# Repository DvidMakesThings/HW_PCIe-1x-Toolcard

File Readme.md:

# PCIe-1x-Toolcard Project

## Contents
This folder contains all the documents related to the PCIe-1x-Toolcard project.

## Usage
To use the files in this project, navigate to the respective directories and follow the instructions provided in each document.

## License
This project is licensed under the GPL-3.0 License. See the [LICENSE](LICENSE) file for details.

## Contact
For questions or feedback:
- Email: [s.dvid@hotmail.com](mailto:s.dvid@hotmail.com)
- GitHub: [DvidMakesThings](https://github.com/DvidMakesThings)

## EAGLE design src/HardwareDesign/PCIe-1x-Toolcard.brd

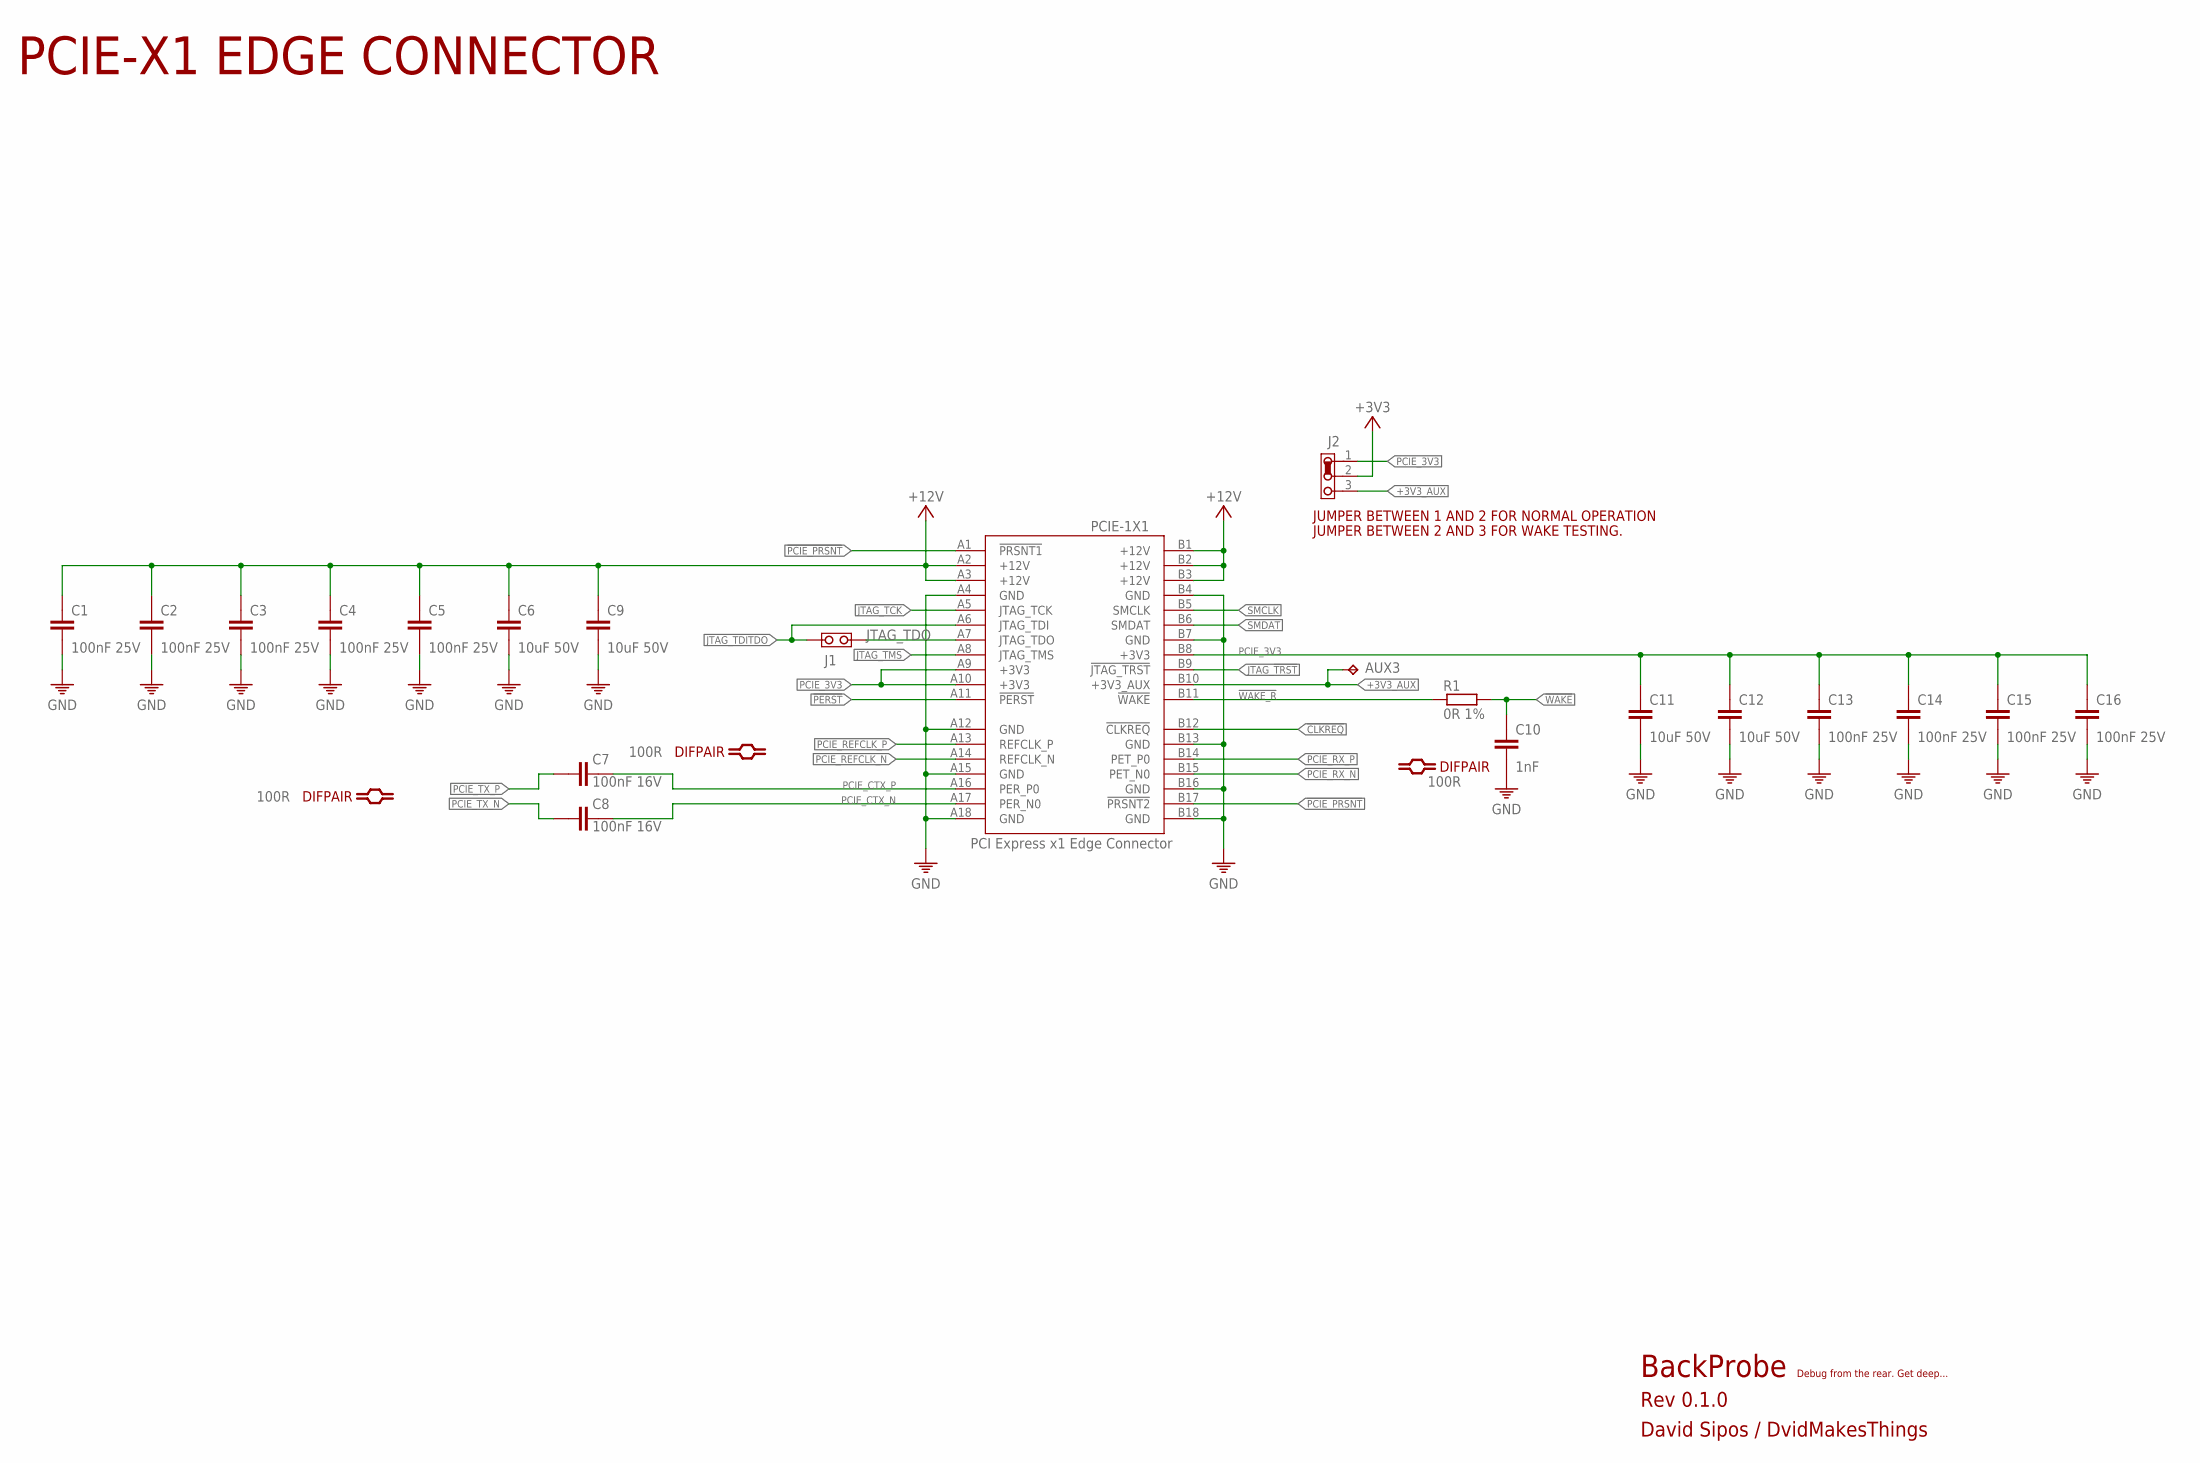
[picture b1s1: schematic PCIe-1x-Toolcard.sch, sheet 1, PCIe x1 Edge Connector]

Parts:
AUX3: TPB1,27; B1,27
C1, C2, C3, C4, C5, C13, C14, C15, C16: 100nF 25V; 0402
C6, C9, C11, C12: 10uF 50V; 0805
C7, C8: 100nF 16V; 0201
C10: 1nF; C0402
J1: JUMPER-NO; J-0402-NO
J2: JUMPER-3
PCIE-1X1: PCI Express x1 Edge Connector; PCIE_X1_LOWPROFILE
R1: 0R 1%; 0201

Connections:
!CLKREQ: PCIE-1X1.B12 (!CLKREQ)
!PCIE_PRSNT: PCIE-1X1.A1 (!PRSNT1), PCIE-1X1.B17 (!PRSNT2)
!PERST: PCIE-1X1.A11 (!PERST); also elsewhere on the board
!WAKE: C10.1, R1.2; also elsewhere on the board
!WAKE_R: PCIE-1X1.B11 (!WAKE), R1.1
+3V3: J2.2; also elsewhere on the board
+3V3_AUX: AUX3.TP, J2.3, PCIE-1X1.B10 (+3V3_AUX)
+12V: C1.1, C2.1, C3.1, C4.1, C5.1, C6.1, C9.1, PCIE-1X1.A2 (+12V), PCIE-1X1.A3 (+12V), PCIE-1X1.B1 (+12V), PCIE-1X1.B2 (+12V), PCIE-1X1.B3 (+12V); also elsewhere on the board
GND: C1.2, C2.2, C3.2, C4.2, C5.2, C6.2, C9.2, C10.2, C11.2, C12.2, C13.2, C14.2, C15.2, C16.2, PCIE-1X1.A4 (GND), PCIE-1X1.A12 (GND), PCIE-1X1.A15 (GND), PCIE-1X1.A18 (GND), PCIE-1X1.B4 (GND), PCIE-1X1.B7 (GND), PCIE-1X1.B13 (GND), PCIE-1X1.B16 (GND), PCIE-1X1.B18 (GND); also elsewhere on the board
JTAG_!TRST: PCIE-1X1.B9 (!JTAG_TRST)
JTAG_TCK: PCIE-1X1.A5 (JTAG_TCK)
JTAG_TDITDO: J1.1, PCIE-1X1.A6 (JTAG_TDI)
JTAG_TDO: J1.2, PCIE-1X1.A7 (JTAG_TDO)
JTAG_TMS: PCIE-1X1.A8 (JTAG_TMS)
PCIE_3V3: C11.1, C12.1, C13.1, C14.1, C15.1, C16.1, J2.1, PCIE-1X1.A9 (+3V3), PCIE-1X1.A10 (+3V3), PCIE-1X1.B8 (+3V3)
PCIE_CTX_N: C8.2, PCIE-1X1.A17 (PER_N0)
PCIE_CTX_P: C7.2, PCIE-1X1.A16 (PER_P0)
PCIE_REFCLK_N: PCIE-1X1.A14 (REFCLK_N); also elsewhere on the board
PCIE_REFCLK_P: PCIE-1X1.A13 (REFCLK_P); also elsewhere on the board
PCIE_RX_N: PCIE-1X1.B15 (PET_N0); also elsewhere on the board
PCIE_RX_P: PCIE-1X1.B14 (PET_P0); also elsewhere on the board
PCIE_TX_N: C8.1; also elsewhere on the board
PCIE_TX_P: C7.1; also elsewhere on the board
SMCLK: PCIE-1X1.B5 (SMCLK)
SMDAT: PCIE-1X1.B6 (SMDAT)

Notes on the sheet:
BackProbe
Rev 0.1.0
David Sipos / DvidMakesThings
Debug from the rear. Get deep...
JUMPER BETWEEN 2 AND 3 FOR WAKE TESTING.
JUMPER BETWEEN 1 AND 2 FOR NORMAL OPERATION
PCIE-X1 EDGE CONNECTOR

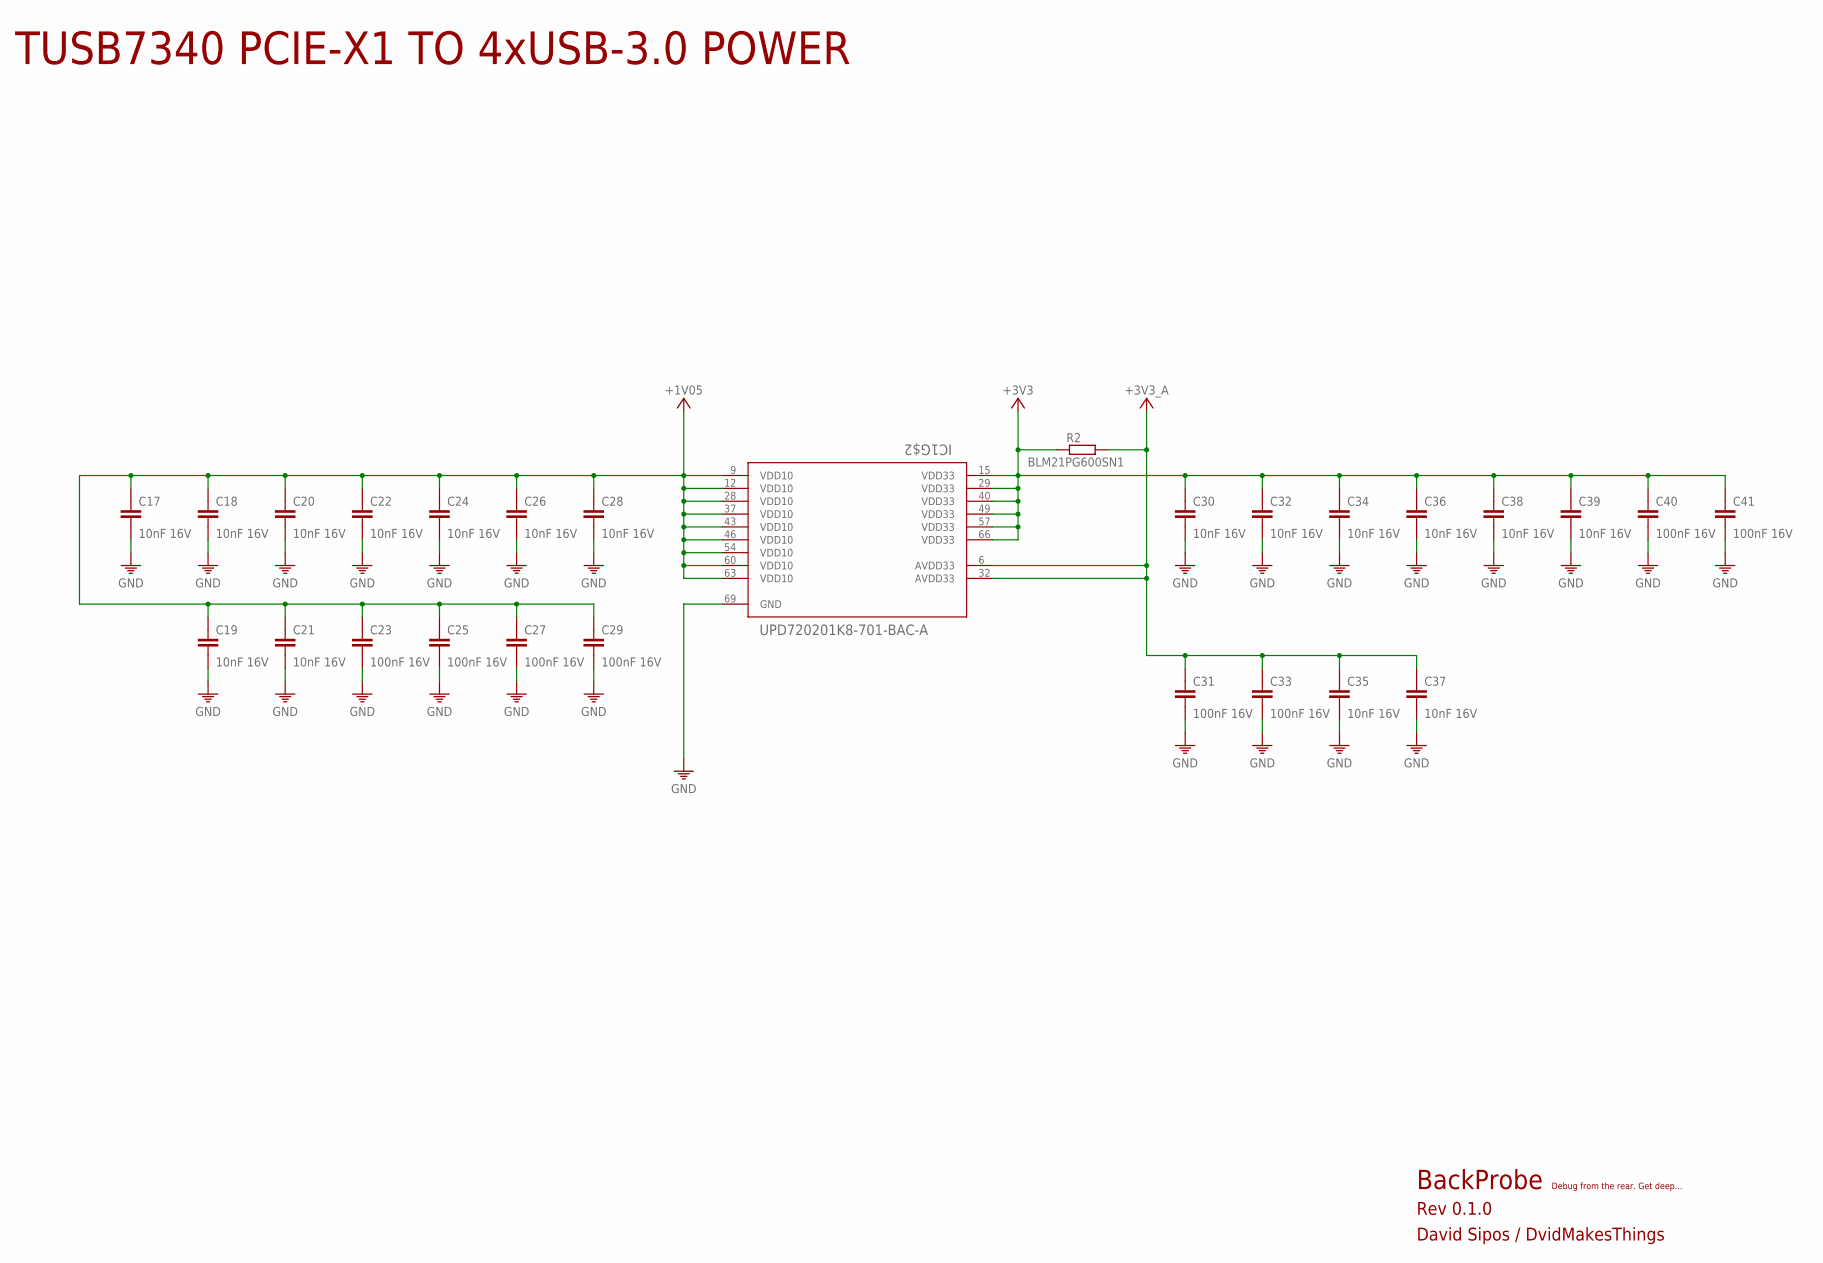
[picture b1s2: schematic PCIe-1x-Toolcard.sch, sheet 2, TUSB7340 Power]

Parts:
C17, C18, C19, C20, C21, C22, C24, C26, C28, C30, C32, C34, C35, C36, C37, C38, C39: 10nF 16V; 0201
C23, C25, C27, C29, C31, C33, C40, C41: 100nF 16V; 0201
IC1: UPD720201K8-701-BAC-A; QFN68-8X8
R2: BLM21PG600SN1; 0603

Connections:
+1V05: C17.1, C18.1, C19.1, C20.1, C21.1, C22.1, C23.1, C24.1, C25.1, C26.1, C27.1, C28.1, C29.1, IC1.9 (VDD10), IC1.12 (VDD10), IC1.28 (VDD10), IC1.37 (VDD10), IC1.43 (VDD10), IC1.46 (VDD10), IC1.54 (VDD10), IC1.60 (VDD10), IC1.63 (VDD10); also elsewhere on the board
+3V3: C30.1, C32.1, C34.1, C36.1, C38.1, C39.1, C40.1, C41.1, IC1.15 (VDD33), IC1.29 (VDD33), IC1.40 (VDD33), IC1.49 (VDD33), IC1.57 (VDD33), IC1.66 (VDD33), R2.1; also elsewhere on the board
+3V3A: C31.1, C33.1, C35.1, C37.1, IC1.6 (AVDD33), IC1.32 (AVDD33), R2.2
GND: C17.2, C18.2, C19.2, C20.2, C21.2, C22.2, C23.2, C24.2, C25.2, C26.2, C27.2, C28.2, C29.2, C30.2, C31.2, C32.2, C33.2, C34.2, C35.2, C36.2, C37.2, C38.2, C39.2, C40.2, C41.2, IC1.69 (GND); also elsewhere on the board

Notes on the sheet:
BackProbe
Rev 0.1.0
David Sipos / DvidMakesThings
Debug from the rear. Get deep...
TUSB7340 PCIE-X1 TO 4xUSB-3.0 POWER

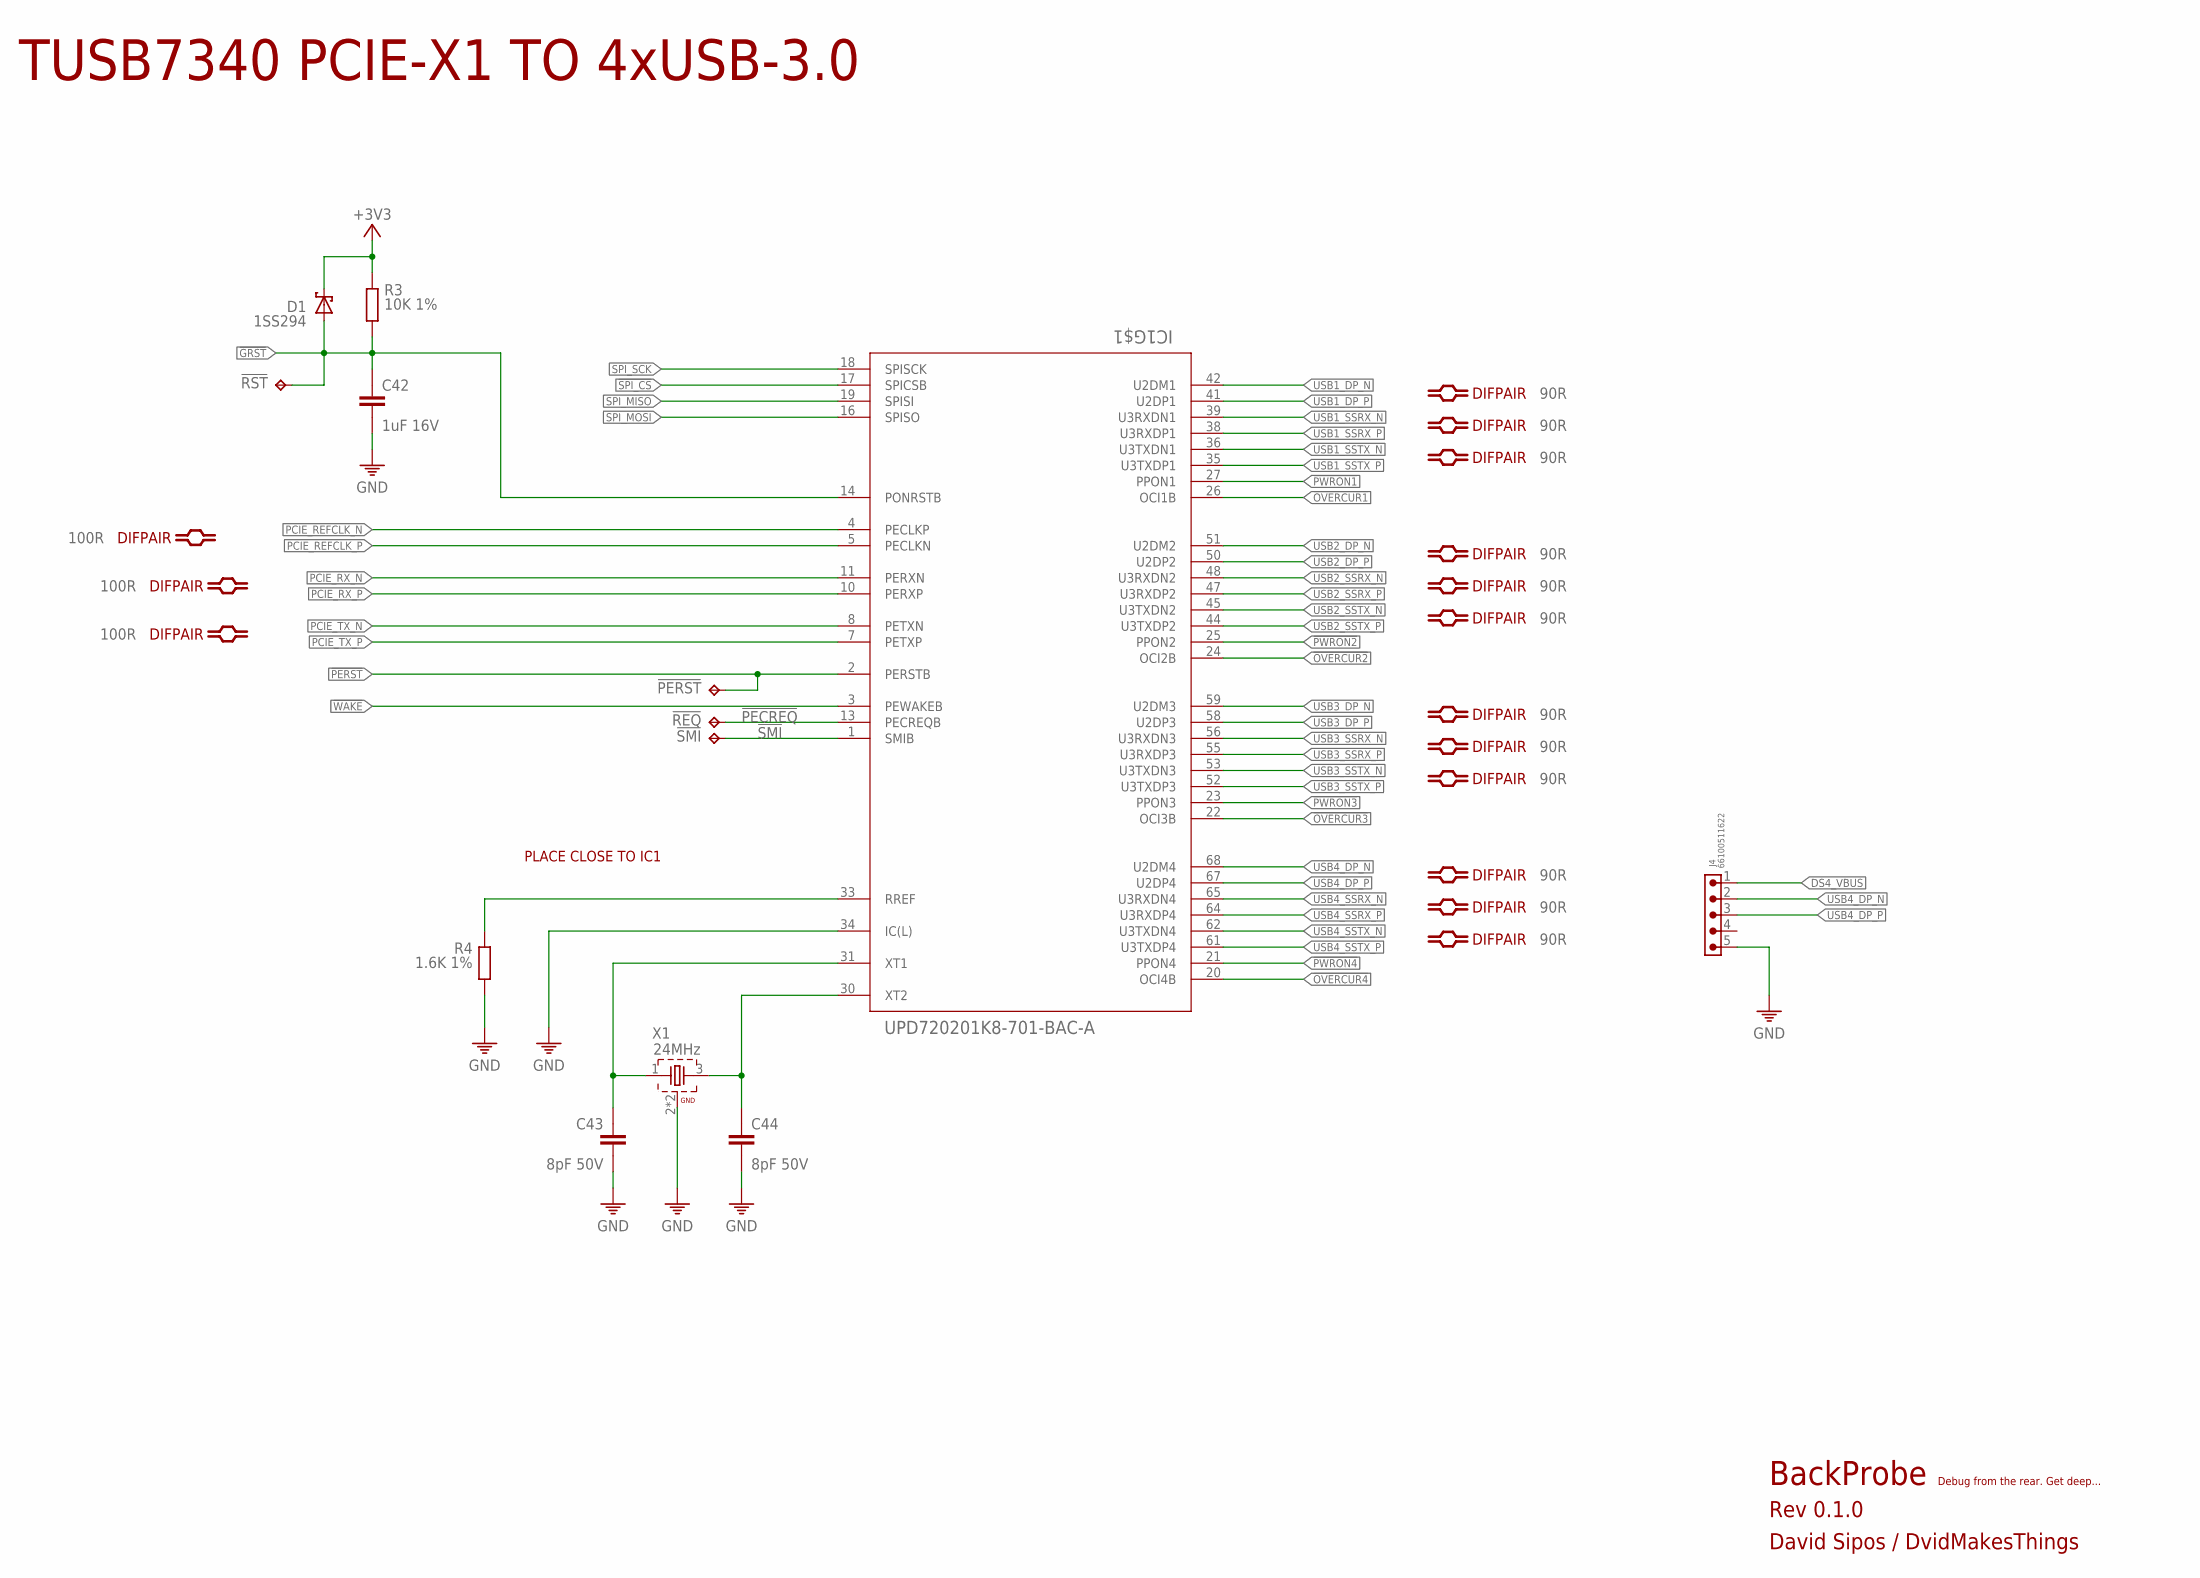
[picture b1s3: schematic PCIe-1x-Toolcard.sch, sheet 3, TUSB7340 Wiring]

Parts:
!PERST: TPB1,27; B1,27
!REQ: TPB1,27; B1,27
!RST: TPB1,27; B1,27
!SMI: TPB1,27; B1,27
C42: 1uF 16V; 0201
C43, C44: 8pF 50V; 0201
D1: 1SS294; SOT23
IC1: UPD720201K8-701-BAC-A; QFN68-8X8
J4: 66100511622
R3: 10K 1%; 0201
R4: 1.6K 1%; 0201
X1: 24MHz; WE-XTAL_CFPX-180

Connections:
!GRST: !RST.TP, C42.1, D1.1 (A), IC1.14 (PONRSTB), R3.2; also elsewhere on the board
!OVERCUR1: IC1.26 (OCI1B); also elsewhere on the board
!OVERCUR2: IC1.24 (OCI2B); also elsewhere on the board
!OVERCUR3: IC1.22 (OCI3B); also elsewhere on the board
!OVERCUR4: IC1.20 (OCI4B); also elsewhere on the board
!PECREQ: !REQ.TP, IC1.13 (PECREQB)
!PERST: !PERST.TP, IC1.2 (PERSTB); also elsewhere on the board
!PWRON1: IC1.27 (PPON1); also elsewhere on the board
!PWRON2: IC1.25 (PPON2); also elsewhere on the board
!PWRON3: IC1.23 (PPON3); also elsewhere on the board
!PWRON4: IC1.21 (PPON4); also elsewhere on the board
!SMI: !SMI.TP, IC1.1 (SMIB)
!SPI_CS: IC1.17 (SPICSB)
!WAKE: IC1.3 (PEWAKEB); also elsewhere on the board
+3V3: D1.3 (C), R3.1; also elsewhere on the board
DS4_VBUS: J4.1; also elsewhere on the board
GND: C42.2, C43.2, C44.2, IC1.34 (IC(L)), J4.5, R4.2, X1.2 (GND), X1.4 (GND); also elsewhere on the board
unnamed: C43.1, IC1.31 (XT1), X1.1
unnamed: C44.1, IC1.30 (XT2), X1.3 (2)
unnamed: IC1.33 (RREF), R4.1
PCIE_REFCLK_N: IC1.4 (PECLKP); also elsewhere on the board
PCIE_REFCLK_P: IC1.5 (PECLKN); also elsewhere on the board
PCIE_RX_N: IC1.11 (PERXN); also elsewhere on the board
PCIE_RX_P: IC1.10 (PERXP); also elsewhere on the board
PCIE_TX_N: IC1.8 (PETXN); also elsewhere on the board
PCIE_TX_P: IC1.7 (PETXP); also elsewhere on the board
SPI_MISO: IC1.19 (SPISI)
SPI_MOSI: IC1.16 (SPISO)
SPI_SCK: IC1.18 (SPISCK)
USB1_DP_N: IC1.42 (U2DM1); also elsewhere on the board
USB1_DP_P: IC1.41 (U2DP1); also elsewhere on the board
USB1_SSRX_N: IC1.39 (U3RXDN1)
USB1_SSRX_P: IC1.38 (U3RXDP1)
USB1_SSTX_N: IC1.36 (U3TXDN1)
USB1_SSTX_P: IC1.35 (U3TXDP1)
USB2_DP_N: IC1.51 (U2DM2); also elsewhere on the board
USB2_DP_P: IC1.50 (U2DP2); also elsewhere on the board
USB2_SSRX_N: IC1.48 (U3RXDN2)
USB2_SSRX_P: IC1.47 (U3RXDP2)
USB2_SSTX_N: IC1.45 (U3TXDN2)
USB2_SSTX_P: IC1.44 (U3TXDP2)
USB3_DP_N: IC1.59 (U2DM3); also elsewhere on the board
USB3_DP_P: IC1.58 (U2DP3); also elsewhere on the board
USB3_SSRX_N: IC1.56 (U3RXDN3)
USB3_SSRX_P: IC1.55 (U3RXDP3)
USB3_SSTX_N: IC1.53 (U3TXDN3)
USB3_SSTX_P: IC1.52 (U3TXDP3)
USB4_DP_N: IC1.68 (U2DM4), J4.2
USB4_DP_P: IC1.67 (U2DP4), J4.3
USB4_SSRX_N: IC1.65 (U3RXDN4)
USB4_SSRX_P: IC1.64 (U3RXDP4)
USB4_SSTX_N: IC1.62 (U3TXDN4)
USB4_SSTX_P: IC1.61 (U3TXDP4)

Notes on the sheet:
BackProbe
Rev 0.1.0
David Sipos / DvidMakesThings
Debug from the rear. Get deep...
PLACE CLOSE TO IC1
TUSB7340 PCIE-X1 TO 4xUSB-3.0

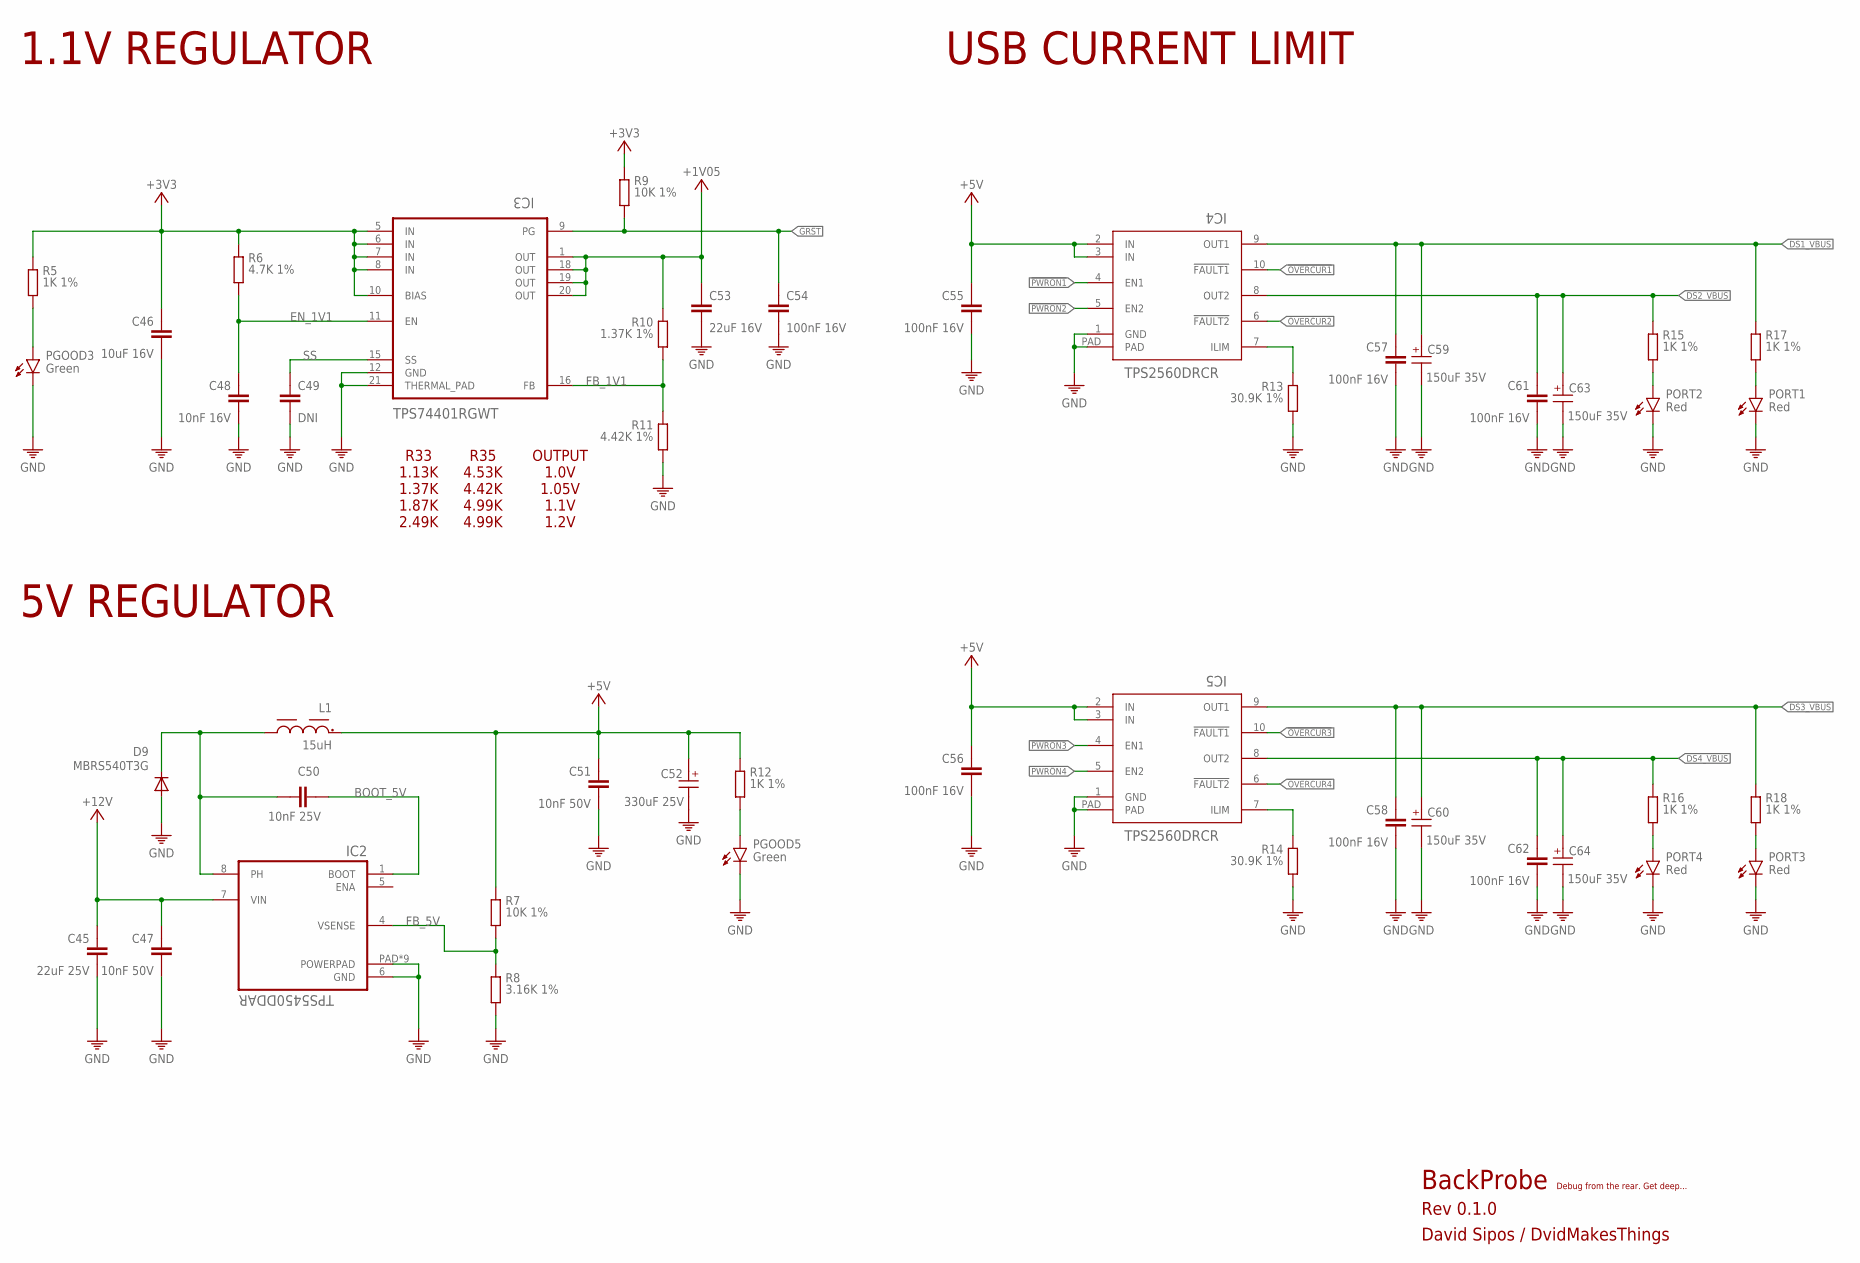
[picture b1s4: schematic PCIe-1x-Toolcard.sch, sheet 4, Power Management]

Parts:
C45: 22uF 25V; 0805
C46: 10uF 16V; 0805
C47, C51: 10nF 50V; 0805
C48: 10nF 16V; 0201
C49: DNI; 0201
C50: 10nF 25V; 0402
C52: 330uF 25V; 6.3X7.7(DXL)
C53: 22uF 16V; 0805
C54, C55, C56, C57, C58, C61, C62: 100nF 16V; 0201
C59, C60, C63, C64: 150uF 35V; 6.3X5.5(DXL)
D9: MBRS540T3G; SMC
IC2: TPS5450DDAR; 8-POWERSOIC
IC3: TPS74401RGWT; VQFN20-5X5
IC4, IC5: TPS2560DRCR; VSON10-3X3
L1: 15uH; L-10X10
PGOOD3, PGOOD5: Green; LED-0603
PORT1, PORT2, PORT3, PORT4: Red; LED-0603
R5, R12, R15, R16, R17, R18: 1K 1%; 0402
R6: 4.7K 1%; 0201
R7: 10K 1%; 0402
R8: 3.16K 1%; 0402
R9: 10K 1%; 0201
R10: 1.37K 1%; 0201
R11: 4.42K 1%; 0201
R13, R14: 30.9K 1%; 0201

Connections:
!GRST: C54.1, IC3.9 (PG), R9.2; also elsewhere on the board
!OVERCUR1: IC4.10 (!FAULT1); also elsewhere on the board
!OVERCUR2: IC4.6 (!FAULT2); also elsewhere on the board
!OVERCUR3: IC5.10 (!FAULT1); also elsewhere on the board
!OVERCUR4: IC5.6 (!FAULT2); also elsewhere on the board
!PWRON1: IC4.4 (EN1); also elsewhere on the board
!PWRON2: IC4.5 (EN2); also elsewhere on the board
!PWRON3: IC5.4 (EN1); also elsewhere on the board
!PWRON4: IC5.5 (EN2); also elsewhere on the board
+1V05: C53.1, IC3.1 (OUT), IC3.18 (OUT), IC3.19 (OUT), IC3.20 (OUT), R10.1; also elsewhere on the board
+3V3: C46.1, IC3.5 (IN), IC3.6 (IN), IC3.7 (IN), IC3.8 (IN), IC3.10 (BIAS), R5.1, R6.1, R9.1; also elsewhere on the board
+5V: C51.1, C52.1 (+), C55.1, C56.1, IC4.2 (IN), IC4.3 (IN), IC5.2 (IN), IC5.3 (IN), L1.1, R7.1, R12.1
+12V: C45.1, C47.1, IC2.7 (VIN); also elsewhere on the board
BOOT_5V: C50.1, IC2.1 (BOOT)
DS1_VBUS: C57.1, C59.1 (+), IC4.9 (OUT1), R17.1; also elsewhere on the board
DS2_VBUS: C61.1, C63.1 (+), IC4.8 (OUT2), R15.1; also elsewhere on the board
DS3_VBUS: C58.1, C60.1 (+), IC5.9 (OUT1), R18.1; also elsewhere on the board
DS4_VBUS: C62.1, C64.1 (+), IC5.8 (OUT2), R16.1; also elsewhere on the board
EN_1V1: C48.1, IC3.11 (EN), R6.2
FB_1V1: IC3.16 (FB), R10.2, R11.1
FB_5V: IC2.4 (VSENSE), R7.2, R8.1
GND: C45.2, C46.2, C47.2, C48.2, C49.2, C51.2, C52.2 (-), C53.2, C54.2, C55.2, C56.2, C57.2, C58.2, C59.2 (-), C60.2 (-), C61.2, C62.2, C63.2 (-), C64.2 (-), D9.A, IC2.6 (GND), IC2.PAD (POWERPAD), IC2.V1 (POWERPAD), IC2.V2 (POWERPAD), IC2.V3 (POWERPAD), IC2.V4 (POWERPAD), IC2.V5 (POWERPAD), IC2.V6 (POWERPAD), IC2.V7 (POWERPAD), IC2.V8 (POWERPAD), IC3.12 (GND), IC3.21 (THERMAL_PAD), IC4.1 (GND), IC4.PAD, IC5.1 (GND), IC5.PAD, PGOOD3.C, PGOOD5.C, PORT1.C, PORT2.C, PORT3.C, PORT4.C, R8.2, R11.2, R13.2, R14.2; also elsewhere on the board
ILIM12: IC4.7 (ILIM), R13.1
ILIM34: IC5.7 (ILIM), R14.1
LEDDS1: PORT2.A, R15.2
LEDDS2: PORT3.A, R18.2
LEDDS3: PORT1.A, R17.2
LEDDS4: PORT4.A, R16.2
LED_3V: PGOOD3.A, R5.2
LED_5V: PGOOD5.A, R12.2
PH: C50.2, D9.C, IC2.8 (PH), L1.2
SS: C49.1, IC3.15 (SS)

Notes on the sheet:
BackProbe
Rev 0.1.0
David Sipos / DvidMakesThings
Debug from the rear. Get deep...
1.1V REGULATOR
5V REGULATOR
USB CURRENT LIMIT
R33 1.13K 1.37K 1.87K 2.49K
R35 4.53K 4.42K 4.99K 4.99K
OUTPUT 1.0V 1.05V 1.1V 1.2V

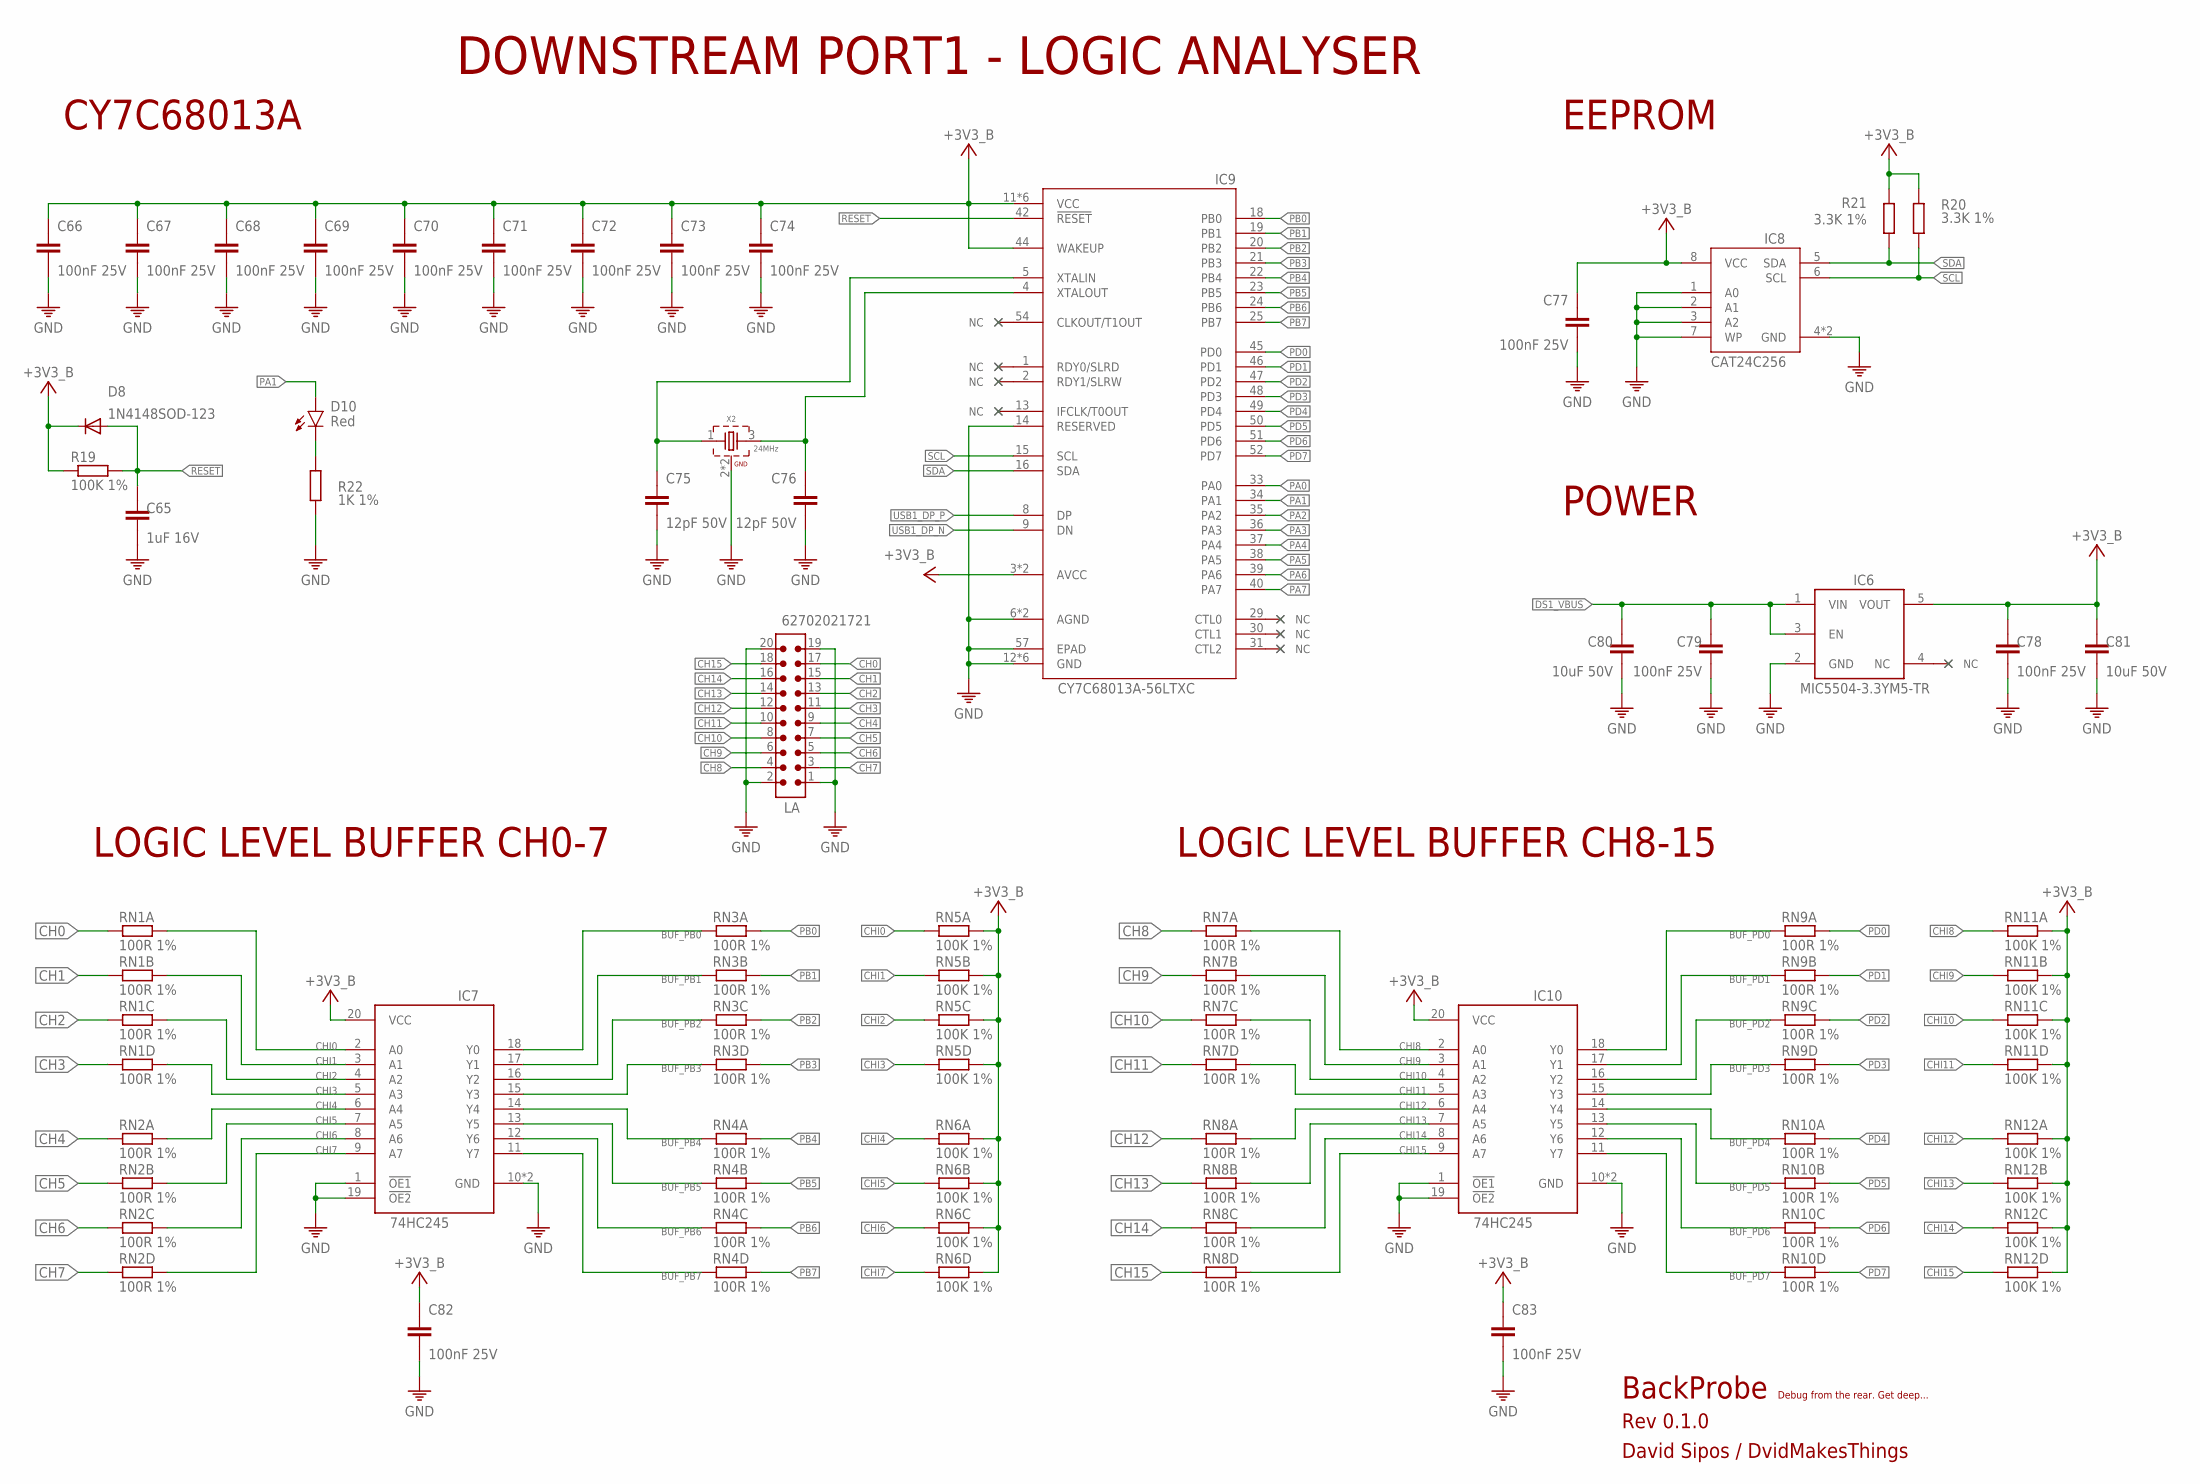
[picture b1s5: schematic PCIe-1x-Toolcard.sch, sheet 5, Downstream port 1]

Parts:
C65: 1uF 16V; 0201
C66, C67, C68, C69, C70, C71, C72, C73, C74, C77, C78, C79, C82, C83: 100nF 25V; 0201
C75, C76: 12pF 50V; 0201
C80, C81: 10uF 50V; 0805
D8: 1N4148SOD-123; SOD-123FL
D10: Red; LED-0603
IC6: MIC5504-3.3YM5-TR; SOT23-5
IC7, IC10: SN74LVC541ARGYR; QFN50P350X450X100-25T305X205N
IC8: CAT24C256HU4IGT3; SON50P300X200X50-9T130X140N
IC9: CY7C68013A-56LTXC; QFN50P800X800X100-57T665
LA: 62702021721
R19: 100K 1%; 0201
R20, R21: 3.3K 1%; 0201
R22: 1K 1%; 0402
RN1, RN2, RN3, RN4, RN7, RN8, RN9, RN10: 100R 1%; 0603X4-1206
RN5, RN6, RN11, RN12: 100K 1%; 0603X4-1206
X2: 24MHz; WE-XTAL_CFPX-180

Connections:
+3V3B: C66.1, C67.1, C68.1, C69.1, C70.1, C71.1, C72.1, C73.1, C74.1, C77.1, C78.1, C81.1, C82.1, C83.1, D8.C, IC6.5 (VOUT), IC7.20 (VCC), IC8.8 (VCC), IC9.3 (AVCC), IC9.7 (AVCC), IC9.11 (VCC), IC9.17 (VCC), IC9.27 (VCC), IC9.32 (VCC), IC9.43 (VCC), IC9.44 (WAKEUP), IC9.55 (VCC), IC10.20 (VCC), R19.1, R20.2, R21.2, RN5.A2 (2), RN5.B2 (2), RN5.C2 (2), RN5.D2 (2), RN6.A2 (2), RN6.B2 (2), RN6.C2 (2), RN6.D2 (2), RN11.A2 (2), RN11.B2 (2), RN11.C2 (2), RN11.D2 (2), RN12.A2 (2), RN12.B2 (2), RN12.C2 (2), RN12.D2 (2)
BUF_PB0: IC7.18 (Y0), RN3.A1 (1)
BUF_PB1: IC7.17 (Y1), RN3.B1 (1)
BUF_PB2: IC7.16 (Y2), RN3.C1 (1)
BUF_PB3: IC7.15 (Y3), RN3.D1 (1)
BUF_PB4: IC7.14 (Y4), RN4.A1 (1)
BUF_PB5: IC7.13 (Y5), RN4.B1 (1)
BUF_PB6: IC7.12 (Y6), RN4.C1 (1)
BUF_PB7: IC7.11 (Y7), RN4.D1 (1)
BUF_PD0: IC10.18 (Y0), RN9.A1 (1)
BUF_PD1: IC10.17 (Y1), RN9.B1 (1)
BUF_PD2: IC10.16 (Y2), RN9.C1 (1)
BUF_PD3: IC10.15 (Y3), RN9.D1 (1)
BUF_PD4: IC10.14 (Y4), RN10.A1 (1)
BUF_PD5: IC10.13 (Y5), RN10.B1 (1)
BUF_PD6: IC10.12 (Y6), RN10.C1 (1)
BUF_PD7: IC10.11 (Y7), RN10.D1 (1)
CH0: LA.17, RN1.A1 (1)
CH1: LA.15, RN1.B1 (1)
CH2: LA.13, RN1.C1 (1)
CH3: LA.11, RN1.D1 (1)
CH4: LA.9, RN2.A1 (1)
CH5: LA.7, RN2.B1 (1)
CH6: LA.5, RN2.C1 (1)
CH7: LA.3, RN2.D1 (1)
CH8: LA.4, RN7.A1 (1)
CH9: LA.6, RN7.B1 (1)
CH10: LA.8, RN7.C1 (1)
CH11: LA.10, RN7.D1 (1)
CH12: LA.12, RN8.A1 (1)
CH13: LA.14, RN8.B1 (1)
CH14: LA.16, RN8.C1 (1)
CH15: LA.18, RN8.D1 (1)
CHI0: IC7.2 (A0), RN1.A2 (2), RN5.A1 (1)
CHI1: IC7.3 (A1), RN1.B2 (2), RN5.B1 (1)
CHI2: IC7.4 (A2), RN1.C2 (2), RN5.C1 (1)
CHI3: IC7.5 (A3), RN1.D2 (2), RN5.D1 (1)
CHI4: IC7.6 (A4), RN2.A2 (2), RN6.A1 (1)
CHI5: IC7.7 (A5), RN2.B2 (2), RN6.B1 (1)
CHI6: IC7.8 (A6), RN2.C2 (2), RN6.C1 (1)
CHI7: IC7.9 (A7), RN2.D2 (2), RN6.D1 (1)
CHI8: IC10.2 (A0), RN7.A2 (2), RN11.A1 (1)
CHI9: IC10.3 (A1), RN7.B2 (2), RN11.B1 (1)
CHI10: IC10.4 (A2), RN7.C2 (2), RN11.C1 (1)
CHI11: IC10.5 (A3), RN7.D2 (2), RN11.D1 (1)
CHI12: IC10.6 (A4), RN8.A2 (2), RN12.A1 (1)
CHI13: IC10.7 (A5), RN8.B2 (2), RN12.B1 (1)
CHI14: IC10.8 (A6), RN8.C2 (2), RN12.C1 (1)
CHI15: IC10.9 (A7), RN8.D2 (2), RN12.D1 (1)
DS1_VBUS: C79.1, C80.1, IC6.1 (VIN), IC6.3 (EN); also elsewhere on the board
GND: C65.2, C66.2, C67.2, C68.2, C69.2, C70.2, C71.2, C72.2, C73.2, C74.2, C75.2, C76.2, C77.2, C78.2, C79.2, C80.2, C81.2, C82.2, C83.2, IC6.2 (GND), IC7.1 (!OE1), IC7.10 (GND), IC7.19 (!OE2), IC7.PAD (GND), IC8.1 (A0), IC8.2 (A1), IC8.3 (A2), IC8.4 (GND), IC8.7 (WP), IC8.9 (GND), IC9.6 (AGND), IC9.10 (AGND), IC9.12 (GND), IC9.14 (RESERVED), IC9.26 (GND), IC9.28 (GND), IC9.41 (GND), IC9.53 (GND), IC9.56 (GND), IC9.57 (EPAD), IC10.1 (!OE1), IC10.10 (GND), IC10.19 (!OE2), IC10.PAD (GND), LA.1, LA.2, LA.19, LA.20, R22.2, X2.2 (GND), X2.4 (GND); also elsewhere on the board
LA_LED: D10.C, R22.1
PA0: IC9.33 (PA0)
PA1: D10.A, IC9.34 (PA1)
PA2: IC9.35 (PA2)
PA3: IC9.36 (PA3)
PA4: IC9.37 (PA4)
PA5: IC9.38 (PA5)
PA6: IC9.39 (PA6)
PA7: IC9.40 (PA7)
PB0: IC9.18 (PB0), RN3.A2 (2)
PB1: IC9.19 (PB1), RN3.B2 (2)
PB2: IC9.20 (PB2), RN3.C2 (2)
PB3: IC9.21 (PB3), RN3.D2 (2)
PB4: IC9.22 (PB4), RN4.A2 (2)
PB5: IC9.23 (PB5), RN4.B2 (2)
PB6: IC9.24 (PB6), RN4.C2 (2)
PB7: IC9.25 (PB7), RN4.D2 (2)
PD0: IC9.45 (PD0), RN9.A2 (2)
PD1: IC9.46 (PD1), RN9.B2 (2)
PD2: IC9.47 (PD2), RN9.C2 (2)
PD3: IC9.48 (PD3), RN9.D2 (2)
PD4: IC9.49 (PD4), RN10.A2 (2)
PD5: IC9.50 (PD5), RN10.B2 (2)
PD6: IC9.51 (PD6), RN10.C2 (2)
PD7: IC9.52 (PD7), RN10.D2 (2)
RESET: C65.1, D8.A, IC9.42 (!RESET), R19.2
SCL: IC8.6 (SCL), IC9.15 (SCL), R20.1
SDA: IC8.5 (SDA), IC9.16 (SDA), R21.1
USB1_DP_N: IC9.9 (DN); also elsewhere on the board
USB1_DP_P: IC9.8 (DP); also elsewhere on the board
XIN: C75.1, IC9.5 (XTALIN), X2.1
XOUT: C76.1, IC9.4 (XTALOUT), X2.3 (2)

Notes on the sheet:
BackProbe
Rev 0.1.0
David Sipos / DvidMakesThings
Debug from the rear. Get deep...
DOWNSTREAM PORT1 - LOGIC ANALYSER
CY7C68013A
EEPROM
POWER
LOGIC LEVEL BUFFER CH0-7
LOGIC LEVEL BUFFER CH8-15

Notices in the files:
parts and their libraries:
Wurth_Quartz Crystals: Copyright: Würth Elektronik
COPYRIGHT: Copyright (C) 2025 Ultra Librarian. All rights reserved.
